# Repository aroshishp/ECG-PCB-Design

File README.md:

This repository contains the project files for designing a PCB of an Electrocardiogram in KiCad.

Images are attached below.

<p align='center'>
  
  <br><br>
  
</p>

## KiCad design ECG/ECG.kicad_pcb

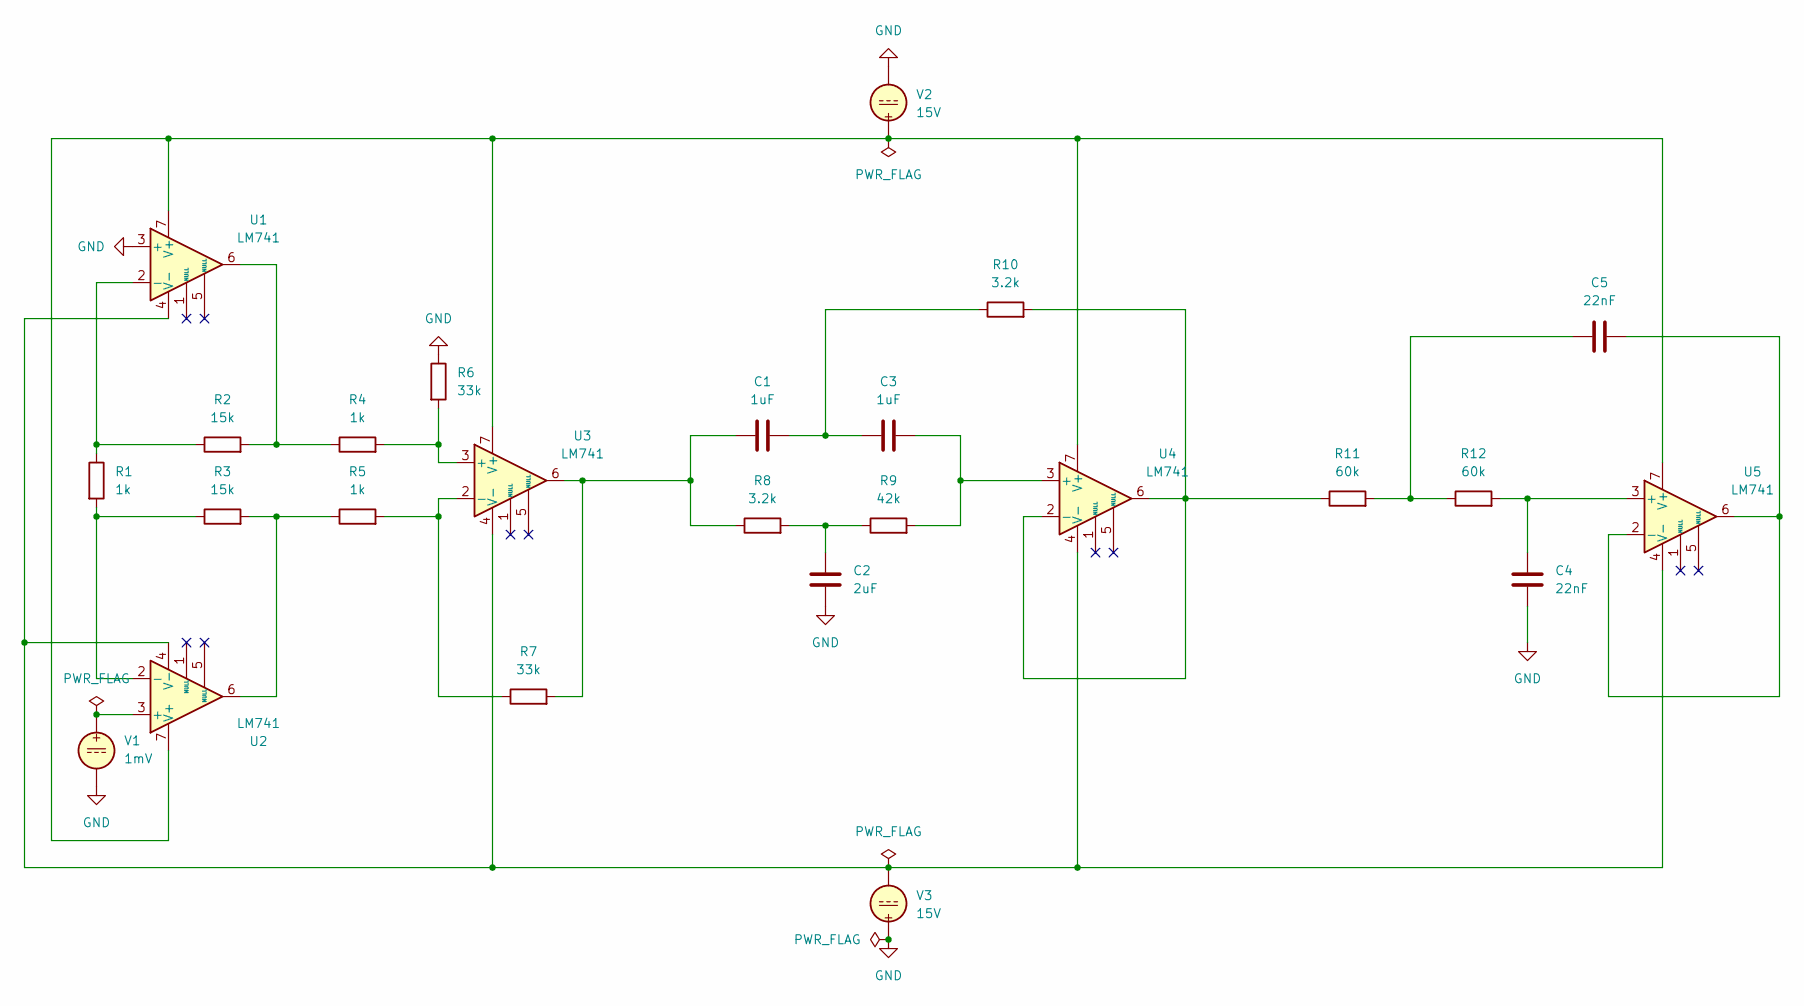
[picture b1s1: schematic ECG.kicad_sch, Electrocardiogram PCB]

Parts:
C1, C3: 1uF; C_Radial_D16.0mm_H31.5mm_P7.50mm
C2: 2uF; C_Radial_D16.0mm_H31.5mm_P7.50mm
C4, C5: 22nF; C_Disc_D5.0mm_W2.5mm_P2.50mm
R1, R4, R5: 1k; R_Axial_DIN0207_L6.3mm_D2.5mm_P15.24mm_Horizontal
R2, R3: 15k; R_Axial_DIN0207_L6.3mm_D2.5mm_P15.24mm_Horizontal
R6, R7: 33k; R_Axial_DIN0207_L6.3mm_D2.5mm_P15.24mm_Horizontal
R8, R10: 3.2k; R_Axial_DIN0207_L6.3mm_D2.5mm_P15.24mm_Horizontal
R9: 42k; R_Axial_DIN0207_L6.3mm_D2.5mm_P15.24mm_Horizontal
R11, R12: 60k; R_Axial_DIN0207_L6.3mm_D2.5mm_P15.24mm_Horizontal
U1, U2, U3, U4, U5: LM741; DIP-8_W7.62mm
V1: 1mV; PinHeader_1x02_P2.54mm_Vertical
V2, V3: 15V; BatteryHolder_Bulgin_BX0036_1xC

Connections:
GND: C2.2, C4.2, R6.1, U1.3 (+), V1.2, V2.2, V3.1
unnamed: C1.1, R7.2, R8.1, U3.6
unnamed: C1.2, C3.1, R10.1
unnamed: C2.1, R8.2, R9.1
unnamed: C5.2, R11.2, R12.1
unnamed: R2.2, R4.1, U1.6
unnamed: R3.2, R5.1, U2.6
unnamed: R1.1, R2.1, U1.2 (-)
unnamed: U1.7 (V+), U2.7 (V+), U3.7 (V+), U4.7 (V+), U5.7 (V+), V2.1
unnamed: U1.4 (V-), U2.4 (V-), U3.4 (V-), U4.4 (V-), U5.4 (V-), V3.2
unnamed: U2.3 (+), V1.1
unnamed: R1.2, R3.1, U2.2 (-)
unnamed: R4.2, R6.2, U3.3 (+)
unnamed: R5.2, R7.1, U3.2 (-)
unnamed: C3.2, R9.2, U4.3 (+)
unnamed: R10.2, R11.1, U4.2 (-), U4.6
unnamed: C4.1, R12.2, U5.3 (+)
unnamed: C5.1, U5.2 (-), U5.6

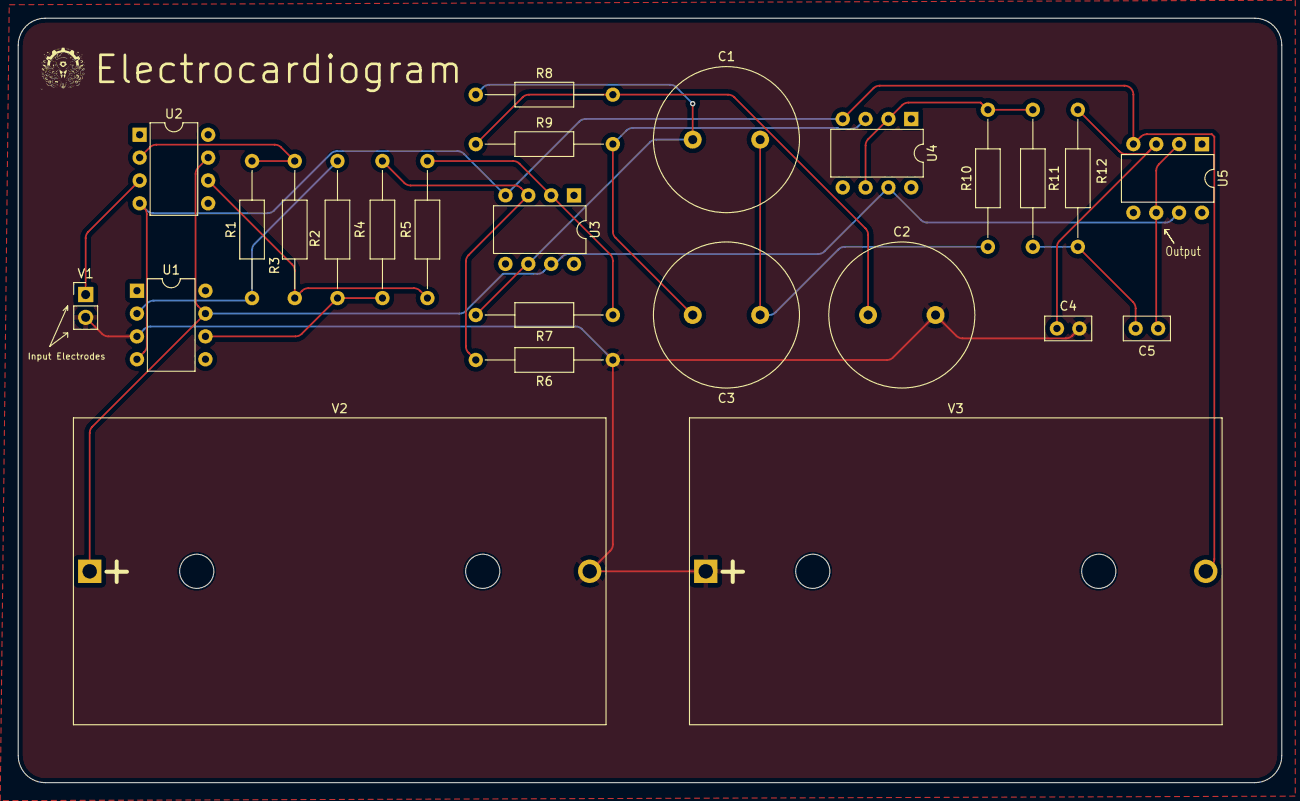
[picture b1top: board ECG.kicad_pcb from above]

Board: 2 copper layers, 140.5 x 85.0 mm, 25 parts (0 on the bottom side), 18 nets.

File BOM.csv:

"Id";"Designator";"Footprint";"Quantity";"Designation";"Supplier and ref";
1;"C3,C1";"C_Radial_D16.0mm_H31.5mm_P7.50mm";2;"1uF";;;
2;"R2,R3";"R_Axial_DIN0207_L6.3mm_D2.5mm_P15.24mm_Horizontal";2;"15k";;;
3;"R9";"R_Axial_DIN0207_L6.3mm_D2.5mm_P15.24mm_Horizontal";1;"42k";;;
4;"C2";"C_Radial_D16.0mm_H31.5mm_P7.50mm";1;"2uF";;;
5;"V3,V2";"BatteryHolder_Bulgin_BX0036_1xC";2;"15V";;;
6;"R8,R10";"R_Axial_DIN0207_L6.3mm_D2.5mm_P15.24mm_Horizontal";2;"165";;;
7;"U1,U5,U4,U2,U3";"DIP-8_W7.62mm";5;"LM741";;;
8;"R11,R12";"R_Axial_DIN0207_L6.3mm_D2.5mm_P15.24mm_Horizontal";2;"60k";;;
9;"C4,C5";"C_Disc_D5.0mm_W2.5mm_P2.50mm";2;"22nF";;;
10;"R6,R7";"R_Axial_DIN0207_L6.3mm_D2.5mm_P15.24mm_Horizontal";2;"33k";;;
11;"V1";"PinHeader_1x02_P2.54mm_Vertical";1;"1mV";;;
12;"R1,R4,R5";"R_Axial_DIN0207_L6.3mm_D2.5mm_P15.24mm_Horizontal";3;"1k";;;
